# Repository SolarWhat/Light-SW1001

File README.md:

# Light-SW1001

Solar What?! is the outcome of ongoing research at the University of Edinburgh.

The product design process has taken place over three continents, with input from solar technicians, end users and energy access practitioners.

In 2017 over 6 million small, solar powered lighting devices were sold worldwide and 1.6 million solar powered lighting devices entered electronic waste flows.

We believe that delivering affordable, clean energy for all can also promote responsible production and consumption.

Our goal is to advocate for sustainable design in the global solar industry and promote the repair, reuse and recycling of solar powered electronics. We are pro-solar, anti-waste.

The Solar What?! Power is one of two products we have designed to champion our research and catalyse discussion around sustainability and repairability in the off-grid solar sector. The repository for our other product, the Solar What Power, can be found [here](https://github.com/SolarWhat/Power-SW2001 "here").

We encourage you to download the files, reproduce the products, make edits, suggest improvements and, most importantly, share your ideas around design for sustainable international development.  

More information about the project and the team behind it can be found on our [website](http://www.solarwhat.xyz/index.php "website").

You can get in touch with the team by emailing info@solarwhat.xyz. 

[User Manual and Tech Specs](http://www.solarwhat.xyz/resources.php "User Manual and Tech Specs")

[Gerber Files, BOM and Firmware Files](https://github.com/SolarWhat/Light-SW1001/tree/master/PCB%20Files "Gerber Files, BOM and Firmware Files")

[CAD Files (stp)](https://github.com/SolarWhat/Light-SW1001/blob/master/Solar%20What%20Light%20Assembly.stp "CAD Files (stp)")

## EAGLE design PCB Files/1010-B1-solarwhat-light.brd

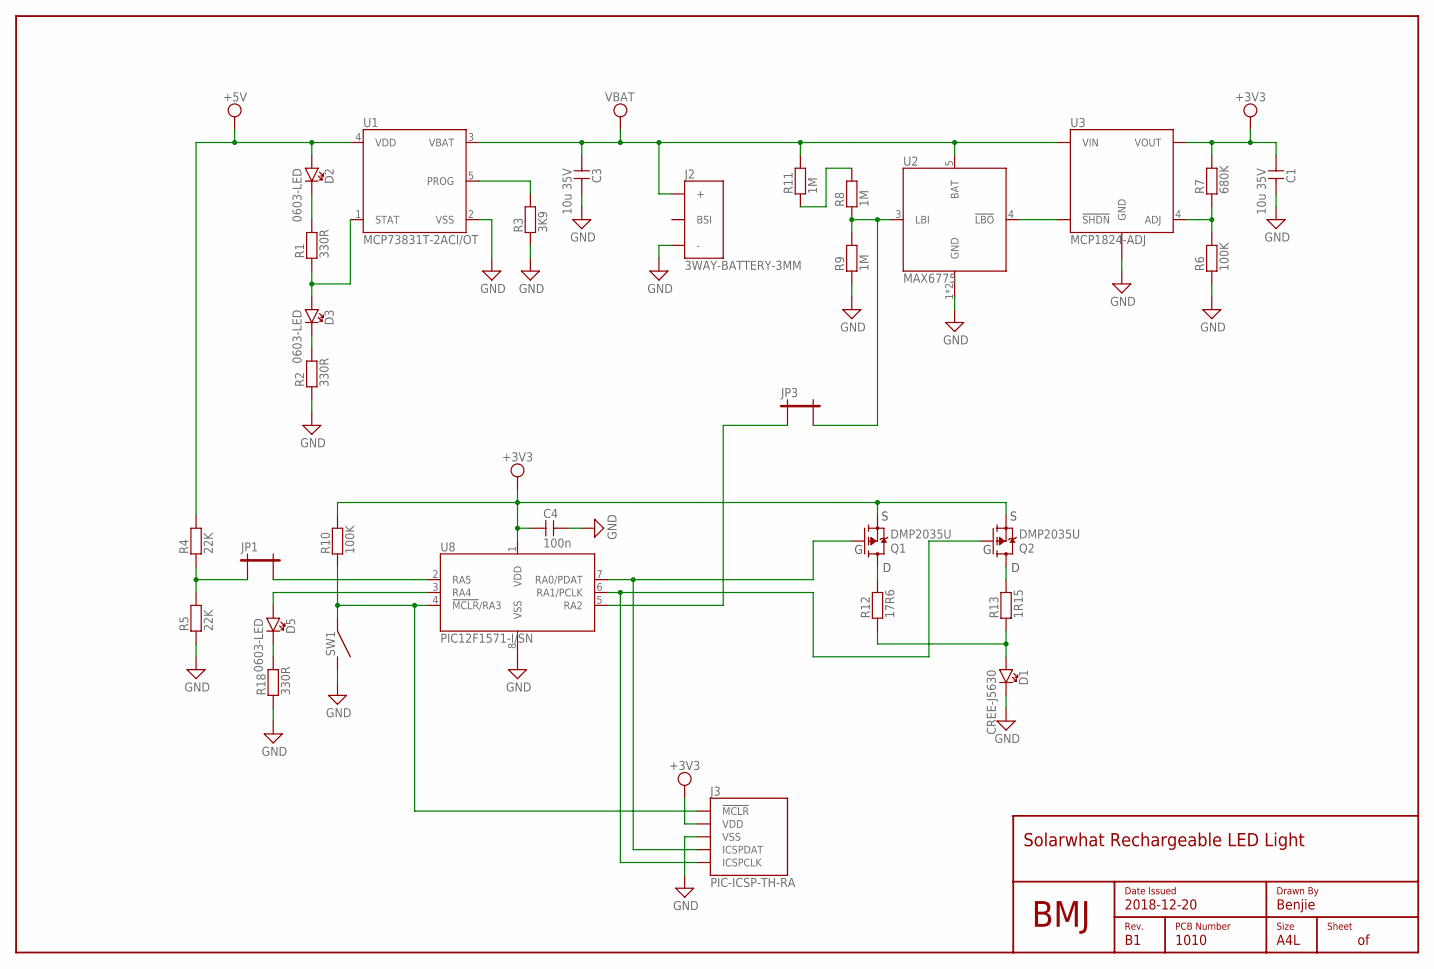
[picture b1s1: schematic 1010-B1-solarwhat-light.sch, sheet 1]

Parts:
C1, C3: 10u 35V; 1206
C4: 100n; 0603
D1: CREE-J5630; MPN Cree JB5630AWT-C0-0000-000A0UC430E
D2: 0603-LED; MPN 0603 orange
D3: 0603-LED; MPN 0603 green
D5: 0603-LED; MPN 0603 red
FRAME1: A4L-NEW; PCB-ID
J2: 3WAY-BATTERY-3MM; 3MM-BATTERY-3WAY
J3: PIC-ICSP-TH-RA
JP1, JP3: SOLDER-JUMPER-1MM-SQUARE; SOLDER-JUMPER-1-1
LOGO1: BMJ-LOGO
Q1, Q2: DMP2035U; SOT-23
R1, R2, R18: 330R; 0603
R3: 3K9; 0603
R4, R5: 22K; 0603
R6, R10: 100K; 0603
R7: 680K; 0603
R8, R9, R11: 1M; 0603
R12: 17R6; 0805
R13: 1R15; 0805
SW1: ALCOSWITCH-FSM4JSMA
U1: MCP73831T-2ACI/OT; SOT-23-5
U2: MAX6775; SC70
U3: MCP1824-ADJ; SOT-23-5
U8: PIC12F1571-I/SN; SOIC-8

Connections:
+3V3: C1.1, C4.1, J3.2 (VDD), Q1.2 (S), Q2.2 (S), R7.2, R10.2, U3.5 (VOUT), U8.1 (VDD)
+5V: D2.A, R4.2, U1.4 (VDD); also elsewhere on the board
GND: C1.2, C3.2, C4.2, D1.K (C), J2.-, J3.3 (VSS), R2.1, R3.1, R5.1, R6.1, R9.1, R18.1, SW1.2@1 (NO), SW1.2@2 (NO), U1.2 (VSS), U2.1 (GND), U2.2 (GND), U3.2 (GND), U8.8 (VSS); also elsewhere on the board
LED_ANODE: D1.A, R12.1, R13.1
unnamed: D3.C, R2.2
unnamed: R3.2, U1.5 (PROG)
unnamed: D3.A, R1.1, U1.1 (STAT)
unnamed: D2.C, R1.2
unnamed: JP1.1, R4.1, R5.2
unnamed: JP1.2, U8.2 (RA5)
unnamed: R6.2, R7.1, U3.4 (ADJ)
unnamed: Q2.3 (D), R13.2
unnamed: JP3.2, R8.1, R9.2, U2.3 (LBI)
unnamed: J3.5 (ICSPCLK), Q2.1 (G), U8.6 (RA1/PCLK)
unnamed: R8.2, R11.1
unnamed: Q1.3 (D), R12.2
unnamed: D5.A, U8.3 (RA4)
unnamed: U2.4 (!LBO), U3.3 (!SHDN)
unnamed: D5.C, R18.2
unnamed: J3.4 (ICSPDAT), Q1.1 (G), U8.7 (RA0/PDAT)
unnamed: J3.1 (!MCLR), R10.1, SW1.1@1 (COM), SW1.1@2 (COM), U8.4 (!MCLR!/RA3)
unnamed: JP3.1, U8.5 (RA2)
VBAT: C3.1, J2.+, R11.2, U1.3 (VBAT), U2.5 (BAT), U3.1 (VIN)

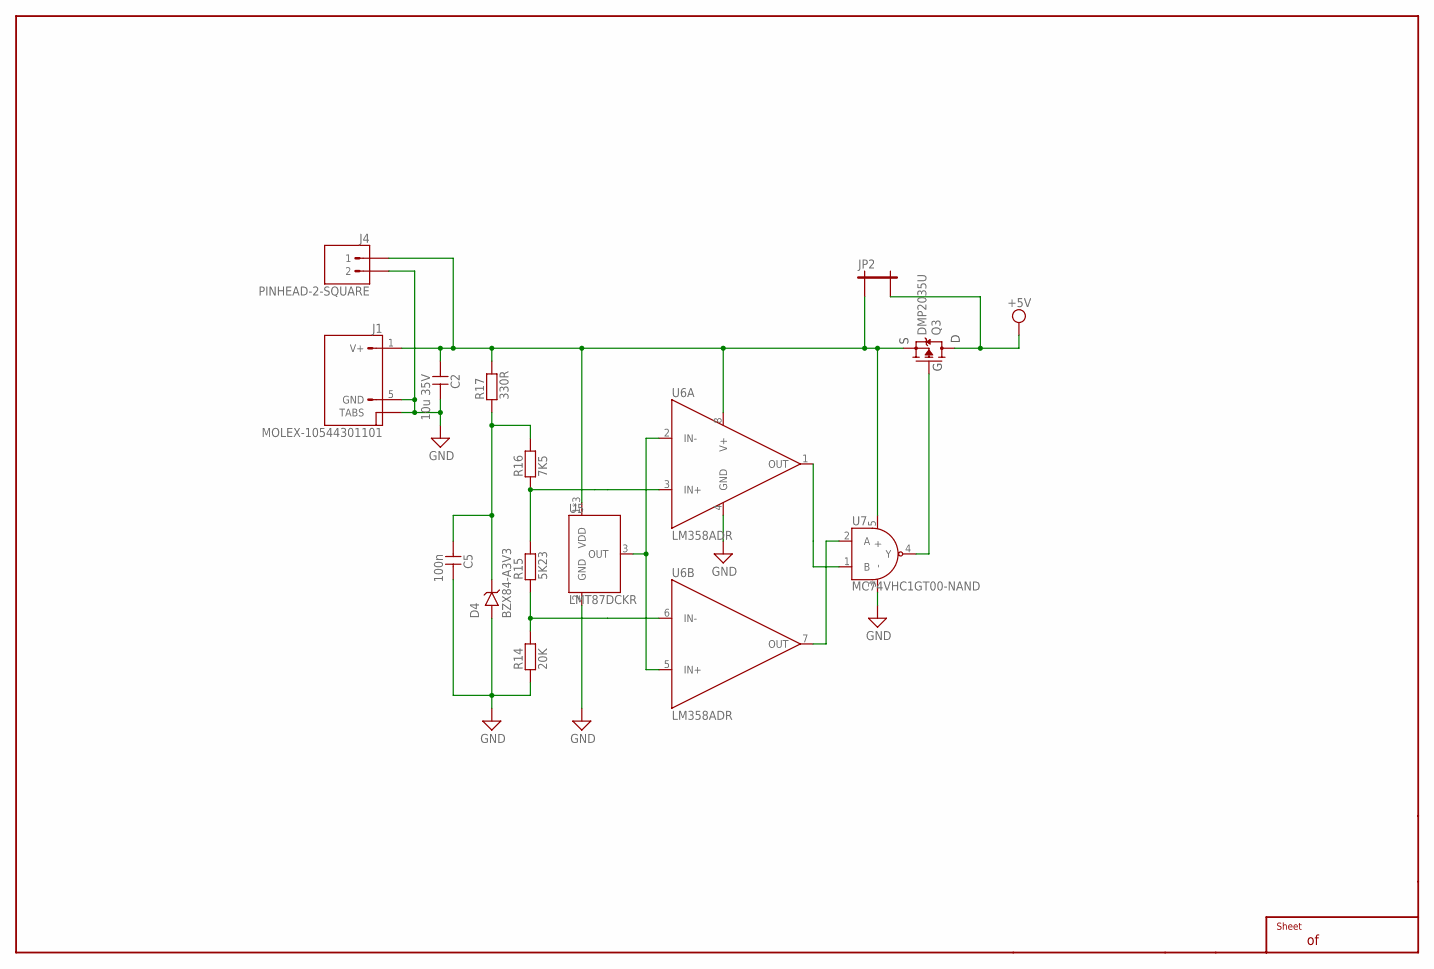
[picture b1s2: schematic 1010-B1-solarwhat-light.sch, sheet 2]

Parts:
C2: 10u 35V; 1206
C5: 100n; 0603
D4: BZX84-A3V3; SOT-23
FRAME2: A4L-CONTINUATION; EMPTY
J1: MOLEX-10544301101; MOLEX-105443-1101-POWERONLY; MPN Molex 10544301-1101
J4: PINHEAD-2-SQUARE
JP2: SOLDER-JUMPER-1MM-SQUARE; SOLDER-JUMPER-1-1
Q3: DMP2035U; SOT-23
R14: 20K; 0603
R15: 5K23; 0603
R16: 7K5; 0603
R17: 330R; 0603
U5: LMT87DCKR; SC70
U6: LM358ADR; SOIC-8
U7: MC74VHC1GT00-NAND; SC70

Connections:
+5V: JP2.2, Q3.3 (D); also elsewhere on the board
GND: C2.2, C5.2, D4.1 (A), J1.5 (GND), J1.GND@1 (TABS), J1.GND@2 (TABS), J1.GND@3 (TABS), J1.GND@4 (TABS), J1.GND@5 (TABS), J1.GND@6 (TABS), J4.2, R14.1, U5.2 (GND), U6.4 (GND), U7.3 (-); also elsewhere on the board
unnamed: C2.1, J1.1 (V+), J4.1, JP2.1, Q3.2 (S), R17.2, U5.1 (VDD), U5.4 (VDD), U5.5 (VDD), U6.8 (V+), U7.5 (+)
unnamed: U6.1 (OUT), U7.1 (B)
unnamed: U6.7 (OUT), U7.2 (A)
unnamed: Q3.1 (G), U7.4 (Y)
unnamed: U5.3 (OUT), U6.2 (IN-), U6.5 (IN+)
unnamed: R14.2, R15.1, U6.6 (IN-)
unnamed: R15.2, R16.1, U6.3 (IN+)
unnamed: C5.1, D4.3 (K), R16.2, R17.1

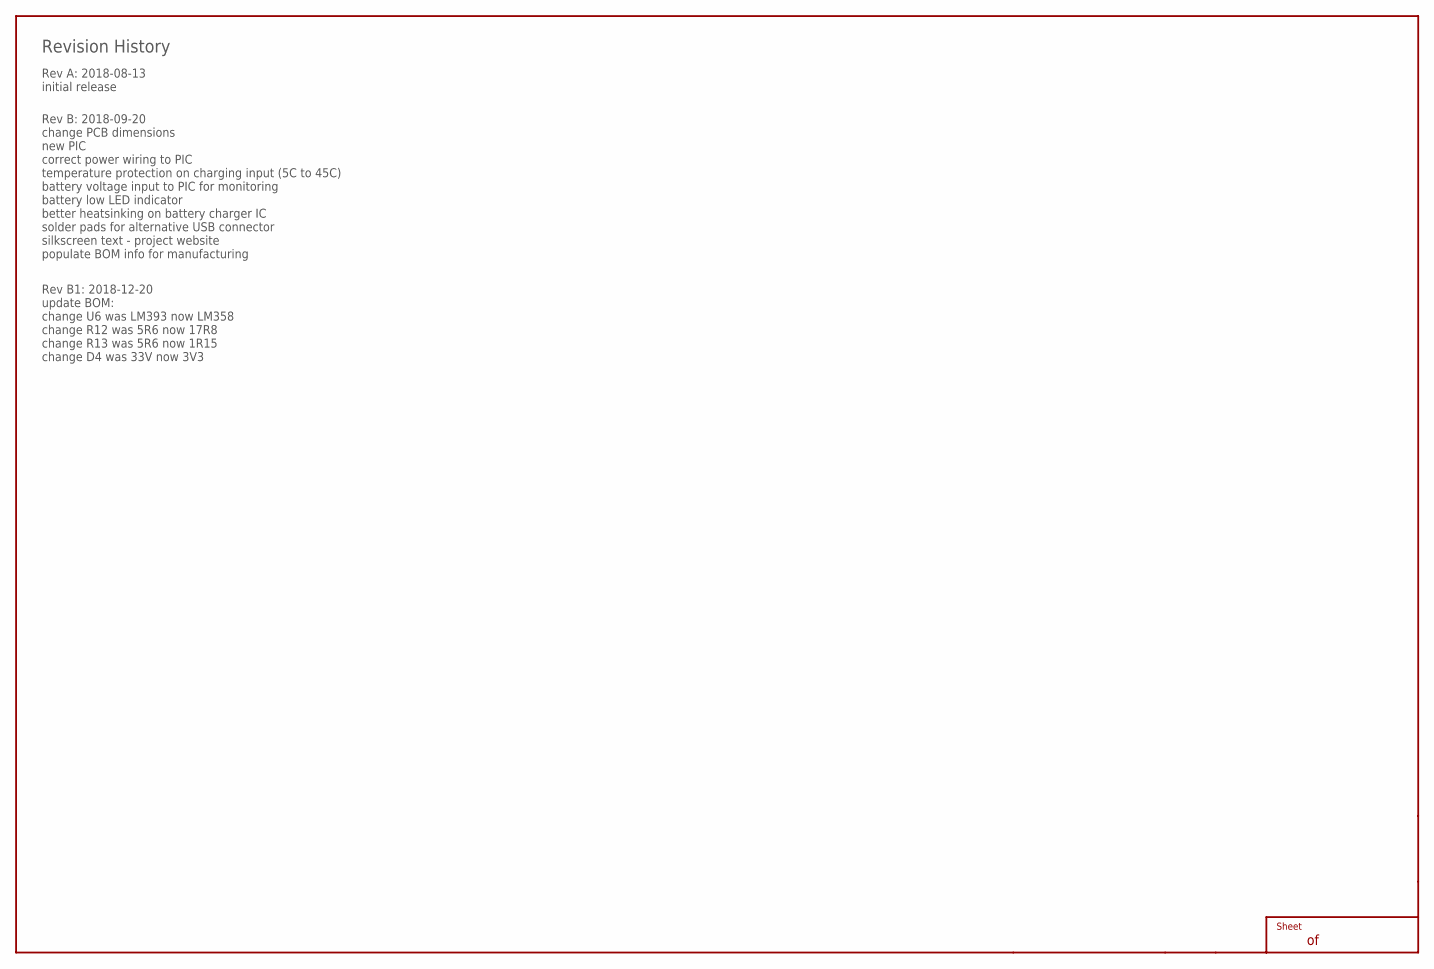
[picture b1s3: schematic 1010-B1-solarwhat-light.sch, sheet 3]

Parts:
FRAME3: A4L-CONTINUATION; EMPTY

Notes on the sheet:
Revision History
Rev A: 2018-08-13 initial release
Rev B: 2018-09-20 change PCB dimensions new PIC correct power wiring to PIC temperature protection on charging input (5C to 45C) battery voltage input to PIC for monitoring battery low LED indicator better heatsinking on battery charger IC solder pads for alternative USB connector silkscreen text -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
Rev B1: 2018-12-20 update BOM: change U6 was LM393 now LM358 change R12 was 5R6 now 17R8 change R13 was 5R6 now 1R15 change D4 was 33V now 3V3

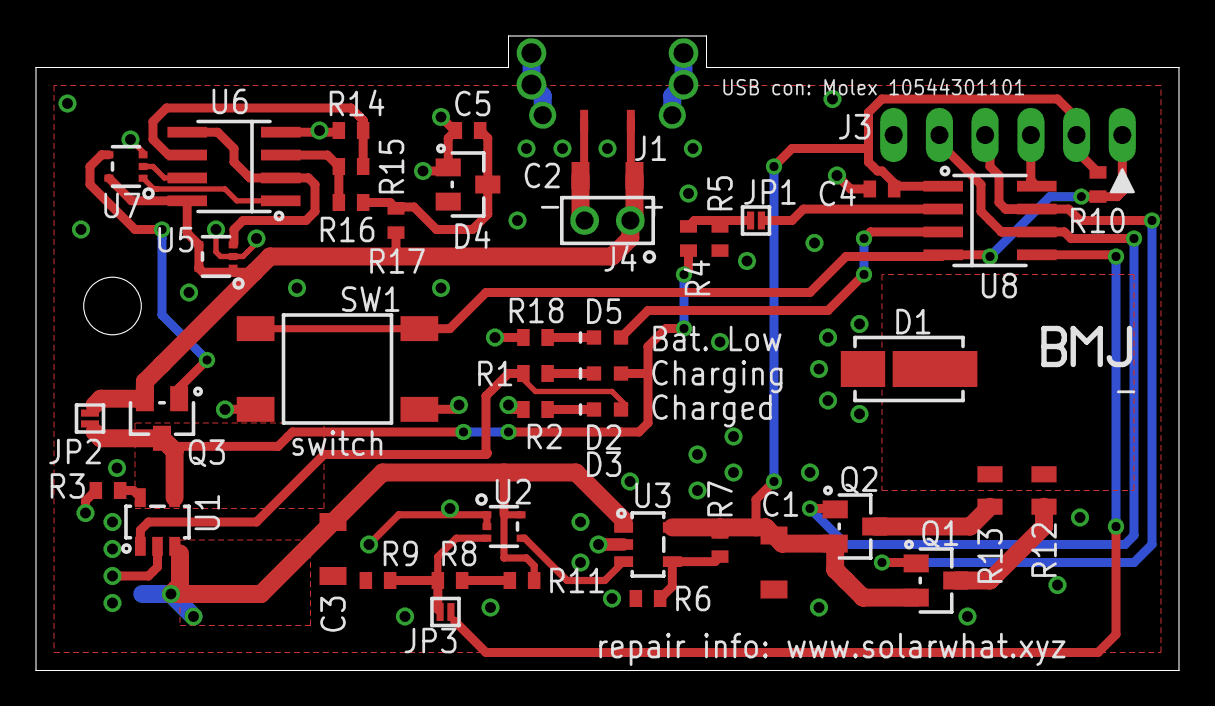
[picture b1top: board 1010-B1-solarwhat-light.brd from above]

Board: 2 copper layers, 63.5 x 35.2 mm, 50 parts (1 on the bottom side), 31 nets.

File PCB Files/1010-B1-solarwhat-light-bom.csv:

"WARNING: This file is auto-generated from schematic, do not edit manually!"
Component,Value,Manufacturer Part Number,Supplier Part Number,Description,Notes
C1,"1206-10U-35V 10u 35V","1206 10uF 35V 10% X7R","standard",,
C2,"1206-10U-35V 10u 35V","1206 10uF 35V 10% X7R","standard",,
C3,"1206-10U-35V 10u 35V","1206 10uF 35V 10% X7R","standard",,
C4,"0603-100N 100n","0603 100nF 50V 10% X7R","standard",,
C5,"0603-100N 100n","0603 100nF 50V 10% X7R","standard",,
D1,,"Cree JB5630AWT-C0-0000-000A0UC430E","Farnell 2853292",,
D2,,"0603 orange","Farnell 2687484",,
D3,,"0603 green","Farnell 2687486",,
D4,,"Nexperia BZX84-A3V3","Farnell 2463632",,
D5,,"0603 red","Farnell 2687488",,
J1,,"Molex 10544301-1101","Farnell 2500017",,
J2,,"AVX 009155003301006","Digi-key 478-4687-1-ND",,
J3,,"PIC-ICSP-TH-RA PIC-ICSP-TH-RA",,,"Do not populate"
J4,,"PINHEAD-2-SQUARE PINHEAD-2-SQUARE",,,"Do not populate"
JP1,,"SOLDER-JUMPER-1MM-SQUARE SOLDER-JUMPER-1-1",,,"Bridge"
JP2,,"SOLDER-JUMPER-1MM-SQUARE SOLDER-JUMPER-1-1",,,"Do not populate"
JP3,,"SOLDER-JUMPER-1MM-SQUARE SOLDER-JUMPER-1-1",,,"Do not populate"
Q1,,"Diodes Inc DMP2035U","Farnell 2061419",,
Q2,,"Diodes Inc DMP2035U","Farnell 2061419",,
Q3,,"Diodes Inc DMP2035U","Farnell 2061419",,
R1,"0603-1%-330R 330R","0603 330R 1% 100mW","standard",,
R2,"0603-1%-330R 330R","0603 330R 1% 100mW","standard",,
R3,"0603-1%-3K9 3K9","0603 3K9 1% 100mW","standard",,
R4,"0603-1%-22K 22K","0603 22K 1% 100mW","standard",,
R5,"0603-1%-22K 22K","0603 22K 1% 100mW","standard",,
R6,"0603-1%-100K 100K","0603 100K 1% 100mW","standard",,
R7,"0603-1%-680K 680K","0603 680K 1% 100mW","standard",,
R8,"0603-1%-1M 1M","0603 1M 1% 100mW","standard",,
R9,"0603-1%-1M 1M","0603 1M 1% 100mW","standard",,
R10,"0603-1%-100K 100K","0603 100K 1% 100mW","standard",,
R11,"0603-1%-1M 1M","0603 1M 1% 100mW","standard",,
R12,"0805-1%-17R6 17R6","0805 17R8 1% 100mW","Farnell 2303354",,
R13,"0805-1%-1R15 1R15","0805 1R15 1% 100mW","Farnell 2141631",,
R14,"0603-1%-20K 20K","0603 20K 1% 100mW","standard",,
R15,"0603-1%-5K23 5K23","0603 5K23 1% 100mW","standard",,
R16,"0603-1%-7K5 7K5","0603 7K5 1% 100mW","standard",,
R17,"0603-1%-330R 330R","0603 330R 1% 100mW","standard",,
R18,"0603-1%-330R 330R","0603 330R 1% 100mW","standard",,
SW1,,"Alcoswitch FSM4JSMA","Farnell 3801305",,
U1,,"Microchip MCP73831T-2ACI/OT","Farnell 1332158",,
U2,,"Maxim MAX6775XKB+T","Farnell 2799268",,
U3,,"Microchip MCP1824T-ADJE/OT","Farnell 1578393",,
U5,,"TI LMT87DCKR","Farnell 2782528",,
U6,,"TI LM358ADR","Farnell 7527007",,
U7,,"On Semi MC74VHC1GT00DF","Farnell 2724115",,
U8,,"Microchip PIC12F1571-I/SN","Farnell 2419682",,

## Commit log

2019-09-15 Hero images
    adding hero images
2019-09-15 test file in folder
    wysiwyg
2019-09-15 test adding hero images
2019-09-15 adding light hero
2019-09-15 update hero image code
2019-09-15 Added text to readme
2019-09-15 Create CC-BY-SA 4.0
    Repository licensing
2019-09-15 Create LICENSE
2019-09-15 Create test
2019-09-15 Added PCB files
    Gerbers, bom etc
2019-09-15 Cad files uploaded
2019-09-30 Readme: Fixing broken link to SW Power repo
